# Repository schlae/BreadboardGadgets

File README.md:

# Breadboard Gadgets

Here are some handy little boards that plug directly into a solderless
breadboard and can be a great help for experiments with digital circuitry.

* ByteHex: Examine an 8-bit data bus, in hex, with numerous latching options.
* ByteDisplay: Similar to above but with 8 discrete LEDs. No microcontroller.
* ByteSwitch: 8-bit DIP switch with pull-up/down resistors.
* ClockGen: A pulse generator that produces a clock up to 1MHz with an adjustable duty cycle. Generates RESET pulses as well.

## Fabbing the boards

Board dimensions are as follows:

* ByteHex: 25.4mm x 20.32mm
* ByteDisplay: 23.4mm x 20.32mm
* ByteSwitch: 23.4mm x 20.32mm
* ClockGen: 32.2mm x 20.32mm

They are all 2-layer designs. Fab them with your favorite color scheme.

Fab files may be found in each board's subdirectory in this repository.

BOMs are the CSV files in each board's subdirectory. Note that jellybean parts like resistors, capacitors, and LEDs have not been assigned Mouser part numbers. Feel free to pull from your junk box.

ClockGen uses super cute little trimmer potentiometers with knobs. The listed Mouser part number is quite expensive, so consider using [this part](https://www.sparkfun.com/products/9806) from Spark Fun instead.

## Building Firmware
The ByteHex and ClockGen boards have an ATMega328PB microcontroller. The code is meant to run without a bootloader and can be built from the command line if you have installed avr-gcc and avrdude.

```
make
make fuses
make prog
```

Note that the avrdude command lines in the makefile are hard-coded for the usbtiny programmer. You'll want to change that if you have another type of AVR programmer.

The MCU is new enough that your version of avr-gcc and avrdude may not
support it yet, see [here](https://gist.github.com/goncalor/51e1c8038cc058b4379552477255b4e1) for instructions on how to fix that.

The bottom of each board has a standard 6-pin AVR programming header as a surface mount footprint. Since you only need to program it once, you could plug a header into the programmer's cable and physically push it up against the board, or you could temporarily tack-solder it in place. You can't really leave the header in place because it may interfere mechanically when you try to plug the board into a breadboard.

## Using the boards

### ClockGen

Adjust the frequency with the upper potentiometer. The lower potentiometer sets the duty cycle. When you set the duty cycle, the percent value will temporarily appear on the display.

The frequency range is set by the knob marked 0, 1, 2, and 3. These settings correspond with the following ranges:

| Range | Frequencies      |
|-------|------------------|
|   0   | 1 to 99Hz        |
|   1   | 100Hz to 999Hz   |
|   2   | 1KHz to 99KHz    |
|   3   | 100KHz to 999KHz |

The rightmost decimal point will light up when the board is generating a reset pulse. The pulse period can be adjusted in the code by changing `RESET_DELAY`, and the reset threshold voltage is set in the code by `VCC_THRESHOLD`.

### ByteHex

Plug the trigger signal into the TRIG jack on the board, or leave it unconnected and set switch 3 to L to display the instantaneous digital value.

There are four configuration switches:

| Switch    | Function            |
|-----------|---------------------|
|   1 (6/9) | Right-side up (up) or upside-down (down) display |
|   2 (R/F) | Trigger on rising (up) or falling (down) edge    | 
|   3 (L/E) | Level sensitive (up) or edge-triggered (down)    | 
|   4 (N/S) | Normal mode (up) or single-shot trigger mode (down) |

The upside-down display is useful if you plug the board into the left side of a breadboard.

The level sensitive mode turns the device into a transparent latch when the trigger input is high (R) or low (F), depending on switch 2.

Single-shot trigger mode captures a single trigger event, freezing the display until you cycle power or change the trigger mode back to normal. This lets you capture a single data byte, something like a simple digital oscilloscope.

### ByteSwitch

This design can be used in a variety of different ways.

* Tie VIN to your 5V rail and GND to ground. Switch ON=logic low.
* Tie VIN to ground and GND to 5V. Switch ON=logic high.
* Use as a miniature resistor twiddle box by leaving the header unconnected and jumpering VIN and GND to your circuit. How can you optimize the values of the resistors?

### ByteDisplay

With the latch input unconnected, the board will drive the LEDs according to the logic levels present on the inputs (transparent latch). You can latch the inputs by connecting a pulse source to the latch input. When the latch input is low, the contents are retained from the last time the latch input was high.

## Licensing

This work is licensed under a Creative Commons Attribution-ShareAlike 4.0 International License. See [https://creativecommons.org/licenses/by-sa/4.0/](https://creativecommons.org/licenses/by-sa/4.0/).

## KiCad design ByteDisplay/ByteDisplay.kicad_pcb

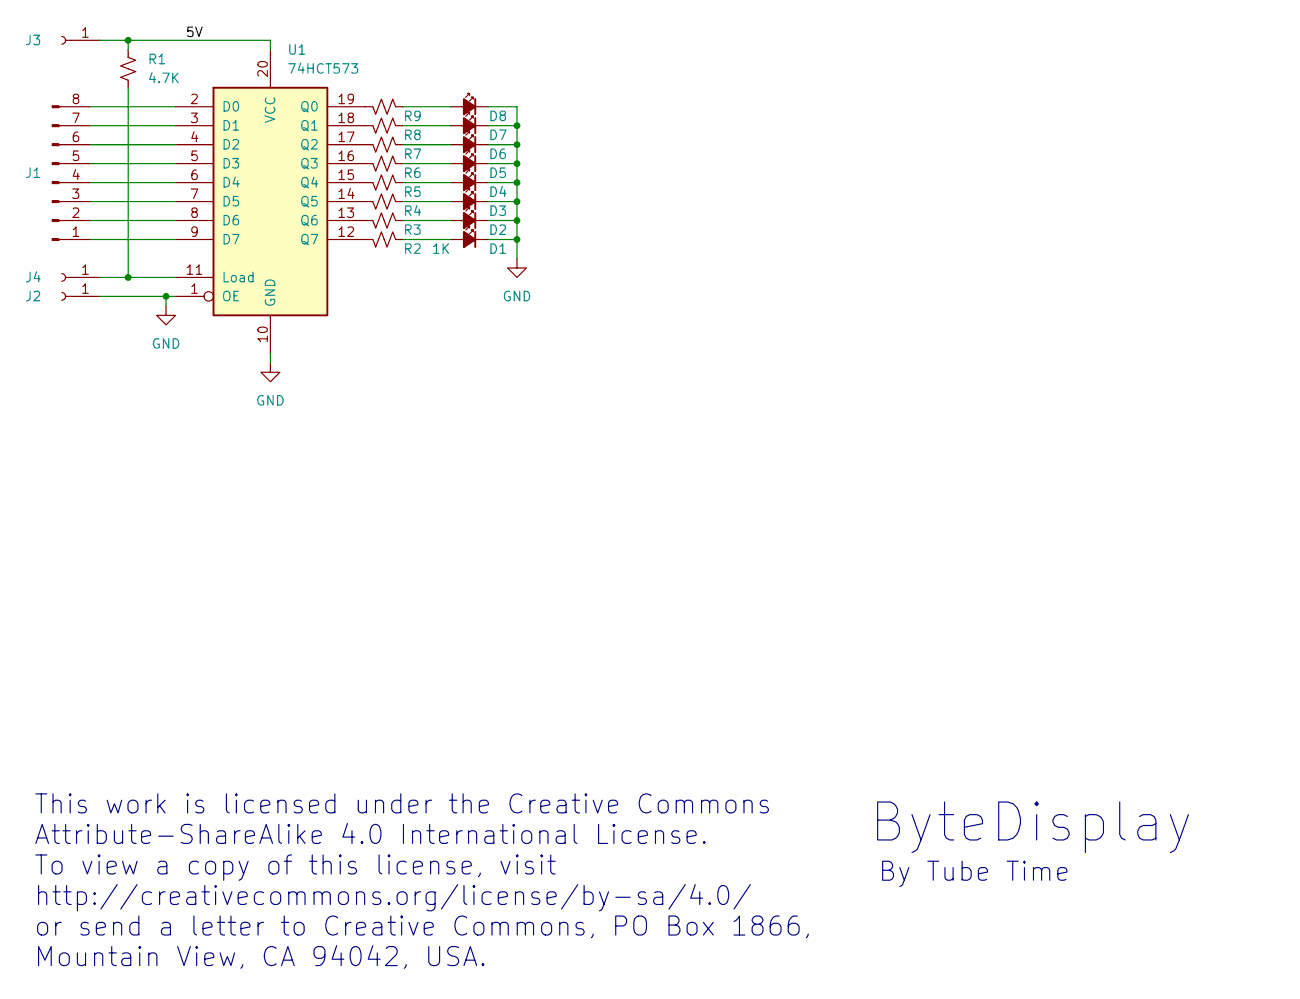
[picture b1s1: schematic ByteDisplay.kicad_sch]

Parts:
D1, D2, D3, D4, D5, D6, D7, D8: LED_Small_Filled; LEDM3216X110; Mouser 859-LTST-C150AKT
J1: Conn_01x08_Pin; PinHeader_1x08_P2.54mm_Vertical
J2, J3, J4: Conn_01x01_Socket; MILL-MAX_0294-0-15-01-06-27-10-0
R1: 4.7K; RESC3216X70
R2, R3, R4, R5, R6, R7, R8, R9: 1K; RESC3216X70
U1: 74HCT573; SOP127P1065X265-20; Mouser 595-SN74HCT573DWR

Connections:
/5V: J3.1, R1.1, U1.20 (VCC)
GND: D1.1 (K), D2.1 (K), D3.1 (K), D4.1 (K), D5.1 (K), D6.1 (K), D7.1 (K), D8.1 (K), J2.1, U1.1 (OE), U1.10 (GND)
unnamed: D1.2 (A), R2.2
unnamed: D2.2 (A), R3.2
unnamed: D3.2 (A), R4.2
unnamed: D4.2 (A), R5.2
unnamed: D5.2 (A), R6.2
unnamed: D6.2 (A), R7.2
unnamed: D7.2 (A), R8.2
unnamed: D8.2 (A), R9.2
unnamed: J1.1, U1.9 (D7)
unnamed: J1.2, U1.8 (D6)
unnamed: J1.3, U1.7 (D5)
unnamed: J1.4, U1.6 (D4)
unnamed: J1.5, U1.5 (D3)
unnamed: J1.6, U1.4 (D2)
unnamed: J1.7, U1.3 (D1)
unnamed: J1.8, U1.2 (D0)
unnamed: J4.1, R1.2, U1.11 (Load)
unnamed: R9.1, U1.19 (Q0)
unnamed: R8.1, U1.18 (Q1)
unnamed: R7.1, U1.17 (Q2)
unnamed: R6.1, U1.16 (Q3)
unnamed: R5.1, U1.15 (Q4)
unnamed: R4.1, U1.14 (Q5)
unnamed: R3.1, U1.13 (Q6)
unnamed: R2.1, U1.12 (Q7)

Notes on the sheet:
This work is licensed under the Creative Commons Attribute-ShareAlike 4.0 International License. To view a copy of this license, visit http://creativecommons.org/license/by-sa/4.0/ or send a letter to Creative Commons, PO Box 1866, Mountain View, CA 94042, USA.
ByteDisplay
By Tube Time

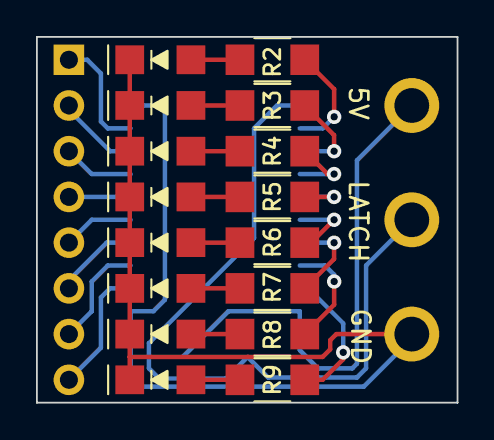
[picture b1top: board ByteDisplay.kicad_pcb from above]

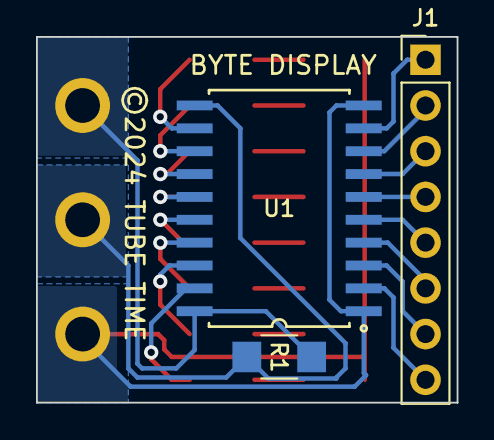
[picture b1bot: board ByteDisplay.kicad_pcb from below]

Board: 2 copper layers, 23.4 x 20.3 mm, 22 parts (3 on the bottom side), 27 nets.

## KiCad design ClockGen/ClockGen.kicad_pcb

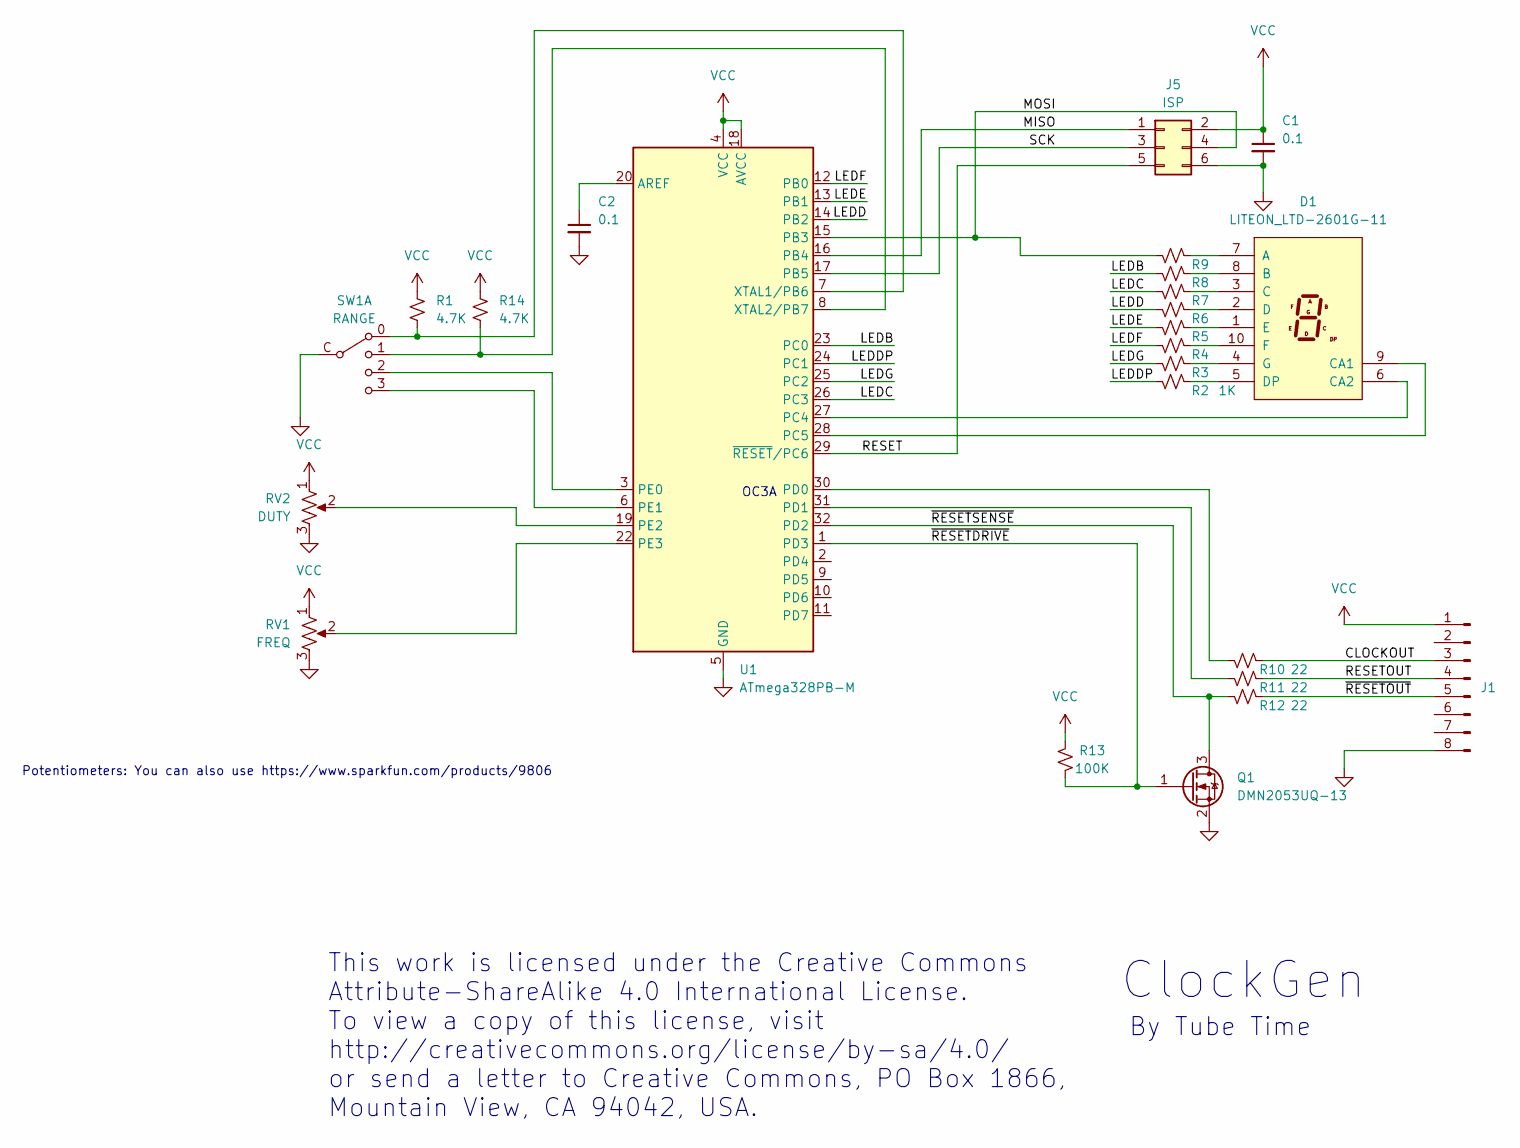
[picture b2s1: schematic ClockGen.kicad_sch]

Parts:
C1, C2: 0.1; CAPC2012X55
D1: LITEON_LTD-2601G-11; LTD-2601G-11; Mouser 859-LTD-2601G-11
J1: Conn_01x08_Pin; PinHeader_1x08_P2.54mm_Vertical
J5: ISP; PinHeader_2x03_P2.54mm_Vertical_SMD
Q1: DMN2053UQ-13; SOT95P230X117-3; Mouser 621-DMN2053UQ-13
R1, R14: 4.7K; RESC2012X55
R2, R3, R4, R5, R6, R7, R8, R9: 1K; RESC2012X55
R10, R11, R12: 22; RESC2012X55
R13: 100K; RESC2012X55
RV1: FREQ; BOURNS_3386_VERT_UNIVERSAL; Mouser 594-63P103T7
RV2: DUTY; BOURNS_3386_VERT_UNIVERSAL; Mouser 594-63P103T7
SW1: RANGE; CTS_220AD_04; Mouser 774-220ADC04
U1: ATmega328PB-M; QFN-32-1EP_5x5mm_P0.5mm_EP3.1x3.1mm; Mouser 556-ATMEGA328PB-MU

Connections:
/CLOCKOUT: J1.3, R10.2
/LEDB: R8.1, U1.23 (PC0)
/LEDC: R7.1, U1.26 (PC3)
/LEDD: R6.1, U1.14 (PB2)
/LEDDP: R2.1, U1.24 (PC1)
/LEDE: R5.1, U1.13 (PB1)
/LEDF: R4.1, U1.12 (PB0)
/LEDG: R3.1, U1.25 (PC2)
/MISO: J5.1, U1.16 (PB4)
/MOSI: J5.4, R9.1, U1.15 (PB3)
/RESET: J5.5, U1.29 (~RESET/PC6)
/RESETOUT: J1.4, R11.2
/SCK: J5.3, U1.17 (PB5)
/~RESETDRIVE: Q1.1 (G), R13.1, U1.1 (PD3)
/~RESETOUT: J1.5, R12.2
/~RESETSENSE: Q1.3 (D), R12.1, U1.32 (PD2)
GND: C1.2, C2.2, J1.8, J5.6, Q1.2 (S), RV1.3, RV2.3, SW1.C, U1.5 (GND), U1.21 (GND), U1.33 (GND)
unnamed: D1.7 (A), R9.2
unnamed: D1.8 (B), R8.2
unnamed: D1.3 (C), R7.2
unnamed: D1.9 (CA1), U1.28 (PC5)
unnamed: D1.6 (CA2), U1.27 (PC4)
unnamed: D1.2 (D), R6.2
unnamed: D1.5 (DP), R2.2
unnamed: D1.1 (E), R5.2
unnamed: D1.10 (F), R4.2
unnamed: D1.4 (G), R3.2
unnamed: C2.1, U1.20 (AREF)
unnamed: R10.1, U1.30 (PD0)
unnamed: R11.1, U1.31 (PD1)
unnamed: SW1.2, U1.3 (PE0)
unnamed: SW1.3, U1.6 (PE1)
unnamed: RV2.2, U1.19 (PE2)
unnamed: RV1.2, U1.22 (PE3)
unnamed: R1.2, SW1.0, U1.7 (XTAL1/PB6)
unnamed: R14.2, SW1.1, U1.8 (XTAL2/PB7)
VCC: C1.1, J1.1, J5.2, R1.1, R13.2, R14.1, RV1.1, RV2.1, U1.4 (VCC), U1.18 (AVCC)

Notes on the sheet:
This work is licensed under the Creative Commons Attribute-ShareAlike 4.0 International License. To view a copy of this license, visit http://creativecommons.org/license/by-sa/4.0/ or send a letter to Creative Commons, PO Box 1866, Mountain View, CA 94042, USA.
Potentiometers: You can also use https://www.sparkfun.com/products/9806
OC3A
ClockGen
By Tube Time

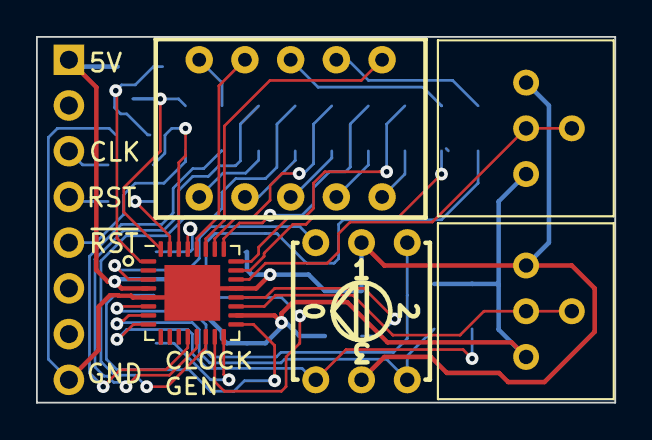
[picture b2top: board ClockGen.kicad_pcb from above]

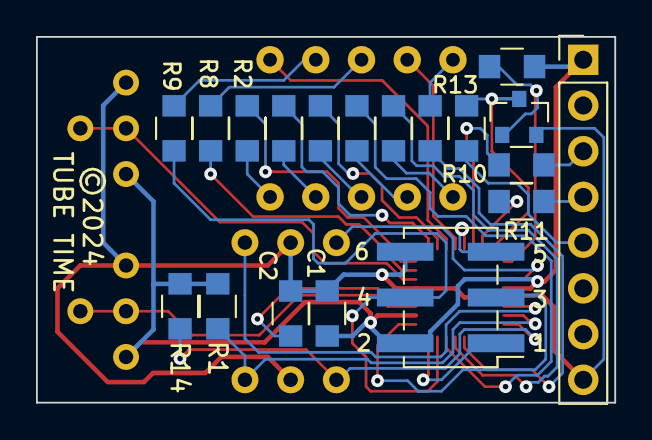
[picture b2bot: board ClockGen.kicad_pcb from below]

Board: 2 copper layers, 32.1 x 20.3 mm, 24 parts (19 on the bottom side), 37 nets.

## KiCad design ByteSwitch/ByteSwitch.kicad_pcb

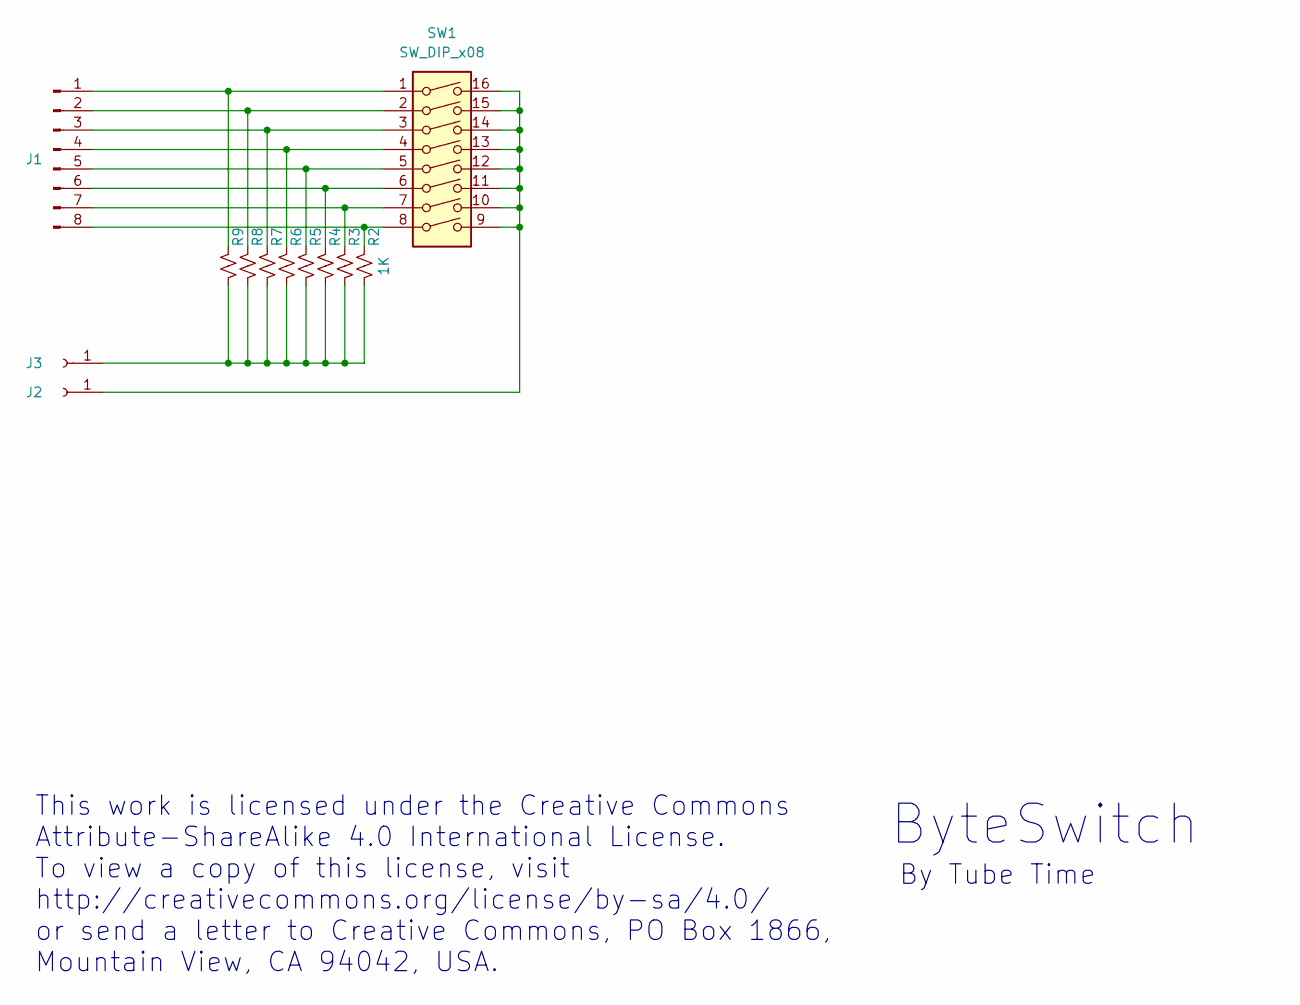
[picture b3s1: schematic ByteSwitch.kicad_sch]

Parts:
J1: Conn_01x08_Pin; PinHeader_1x08_P2.54mm_Vertical
J2, J3: Conn_01x01_Socket; MILL-MAX_0294-0-15-01-06-27-10-0
R2, R3, R4, R5, R6, R7, R8, R9: 1K; RESC3216X70
SW1: SW_DIP_x08; DIP254P762X635-16

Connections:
unnamed: J1.1, R9.2, SW1.1
unnamed: J1.2, R8.2, SW1.2
unnamed: J1.3, R7.2, SW1.3
unnamed: J1.4, R6.2, SW1.4
unnamed: J1.5, R5.2, SW1.5
unnamed: J1.6, R4.2, SW1.6
unnamed: J1.7, R3.2, SW1.7
unnamed: J1.8, R2.2, SW1.8
unnamed: J2.1, SW1.9, SW1.10, SW1.11, SW1.12, SW1.13, SW1.14, SW1.15, SW1.16
unnamed: J3.1, R2.1, R3.1, R4.1, R5.1, R6.1, R7.1, R8.1, R9.1

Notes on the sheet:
By Tube Time
ByteSwitch
This work is licensed under the Creative Commons Attribute-ShareAlike 4.0 International License. To view a copy of this license, visit http://creativecommons.org/license/by-sa/4.0/ or send a letter to Creative Commons, PO Box 1866, Mountain View, CA 94042, USA.

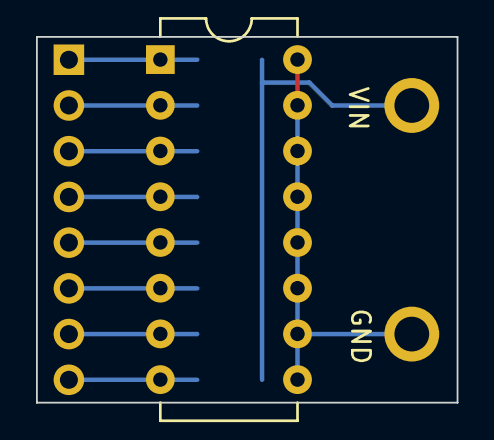
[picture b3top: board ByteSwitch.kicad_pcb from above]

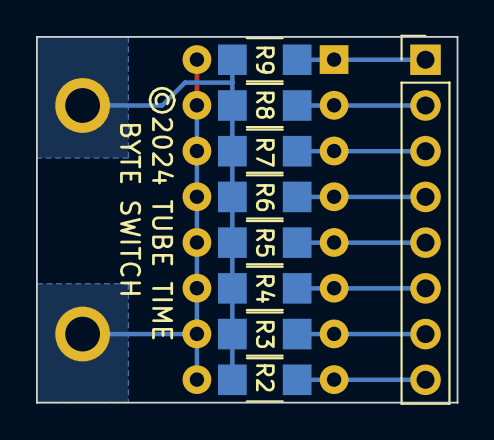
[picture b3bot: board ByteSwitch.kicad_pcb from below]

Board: 2 copper layers, 23.4 x 20.3 mm, 12 parts (9 on the bottom side), 10 nets.

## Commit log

2024-02-17 Code cleanup
2024-02-17 Add board photos
2024-02-17 Add pullup resistors to ClockGen and ByteHex
2024-02-17 Add schematic prints and BOMs

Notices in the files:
ByteDisplay/ByteDisplay.kicad_pcb:
©2024 TUBE TIME
ClockGen/ClockGen.kicad_pcb:
©2024
